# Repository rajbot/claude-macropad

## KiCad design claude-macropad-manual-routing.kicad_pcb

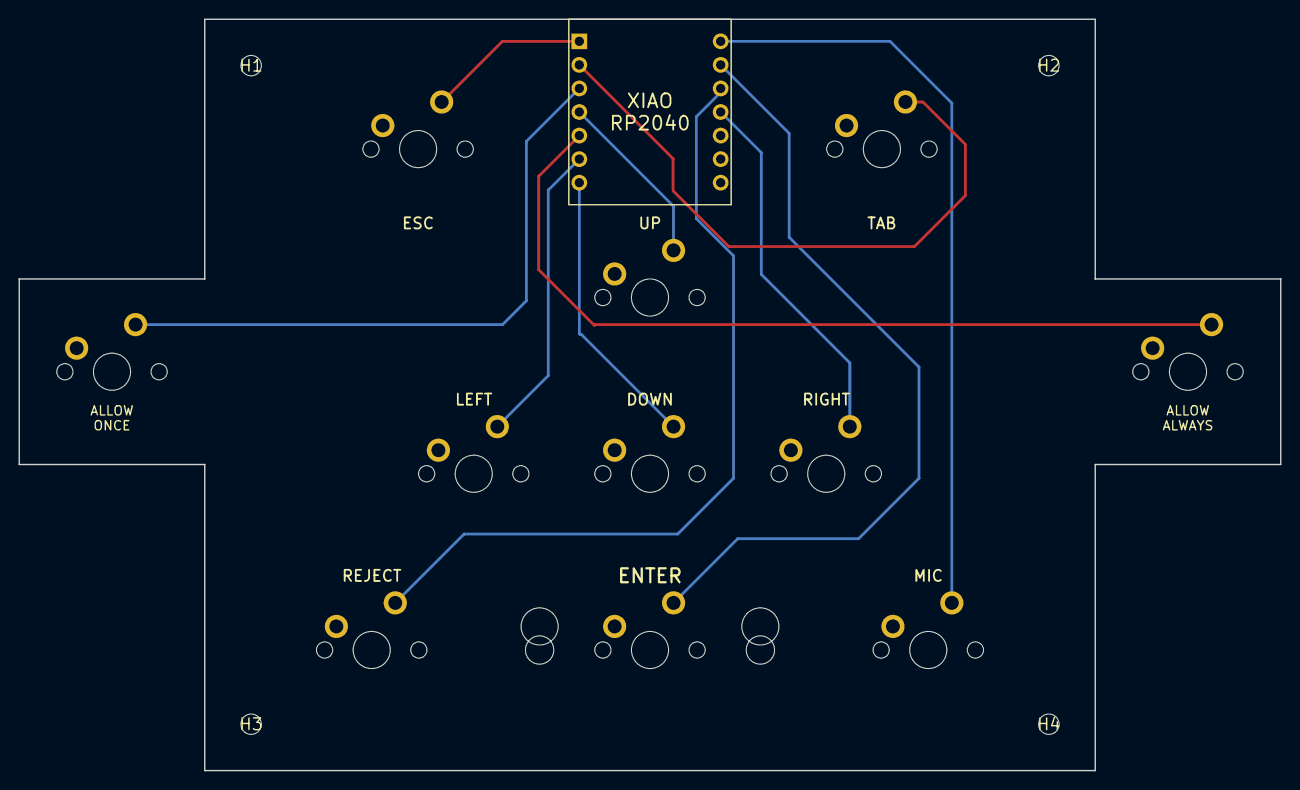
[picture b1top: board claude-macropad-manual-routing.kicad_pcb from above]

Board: 2 copper layers, 136.0 x 81.0 mm, 16 parts (0 on the bottom side), 12 nets.

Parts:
H1, H2, H3, H4: MountingHole_2.2mm_M2
SW1: ESC; SW_Cherry_MX_1u
SW2: TAB; SW_Cherry_MX_1u
SW3: ALLOW_ONCE; SW_Cherry_MX_1u
SW4: UP; SW_Cherry_MX_1u
SW5: ALLOW_ALWAYS; SW_Cherry_MX_1u
SW6: LEFT; SW_Cherry_MX_1u
SW7: DOWN; SW_Cherry_MX_1u
SW8: RIGHT; SW_Cherry_MX_1u
SW9: REJECT; SW_Cherry_MX_1u
SW10: ENTER; SW_Cherry_MX_2u
SW11: MIC; SW_Cherry_MX_1u
U1: XIAO_RP2040; SeeedStudio_XIAO_RP2040

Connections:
GND: SW1.1, SW2.1, SW3.1, SW4.1, SW5.1, SW6.1, SW7.1, SW8.1, SW9.1, SW10.1, SW11.1, U1.13
SW_ALLOW_ALWAYS: SW5.2, U1.5
SW_ALLOW_ONCE: SW3.2, U1.3
SW_DOWN: SW7.2, U1.7
SW_ENTER: SW10.2, U1.9
SW_ESC: SW1.2, U1.1
SW_LEFT: SW6.2, U1.6
SW_MIC: SW11.2, U1.8
SW_REJECT: SW9.2, U1.10
SW_RIGHT: SW8.2, U1.11
SW_TAB: SW2.2, U1.2
SW_UP: SW4.2, U1.4
